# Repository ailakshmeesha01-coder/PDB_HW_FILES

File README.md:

# PDB Hardware Files

KiCad hardware design files for the **NEXUS Power Distribution Board (PDB) V2.0**. The board takes power from a 12S battery (50.4 V max) and distributes it to the humanoid's actuators through 12 XT60 outputs. It precharges the bus, discharges it when powered off, and has a charging input.

**Status:** schematic complete, PCB routed, Gerbers and BOM generated.

## Repository contents

| File / folder | Description |
|---|---|
| `PDB_2.0.kicad_pro` | KiCad project file (open this one) |
| `PDB_2.0.kicad_sch` | Schematic |
| `PDB_2.0.kicad_pcb` | PCB layout (2 layers, 4 oz copper) |
| `PDB_2.0_BOM.xlsx` | Bill of materials |
| `PDB_2.0 Gerber files.zip` | Gerber and drill files for fabrication |
| `NEXUS_PDB_V2_power_simulation.pdf` | Power copper simulation report (current and temperature) |
| `fp-lib-table`, `sym-lib-table` | Project footprint and symbol library tables |
| `Libraries/` | Symbols, footprints and 3D models used by the project |

## Work done

- **Schematic:** full wiring with ERC; precharge, discharge and charging circuits; precharge and charging indicator LEDs added; C21 increased to 1 µF for a reliable power-on reset.
- **PCB layout:** placement, routing and branding; power tracks widened; solid copper pours on the power nets.
- **Main current path:** fixed the via bottleneck between the top-layer MOSFETs and the bottom-layer pours. Added a solid BUS+ pour on F.Cu and more vias on the MOSFET drain and source sides; removed stacked duplicate vias.
- **Connectors:** fixed the XT30 footprint mismatch; added the QS8-S battery connector (J13) and XT90 footprints to `Libraries/`.
- **Assembly:** thermal relief on small SMD GND pads for easier hand soldering; large power pads stay solid.
- **Simulation:** checked the power copper at 100 A continuous and 300 A pulses (see the PDF).
- **Outputs:** Gerbers, 3D models and BOM generated.
- **Project:** files renamed from `PDC_new` to `PDB_2.0`; libraries moved into `Libraries/`.

## Simulation results (summary)

- **100 A continuous** works with a small fan (~1 m/s airflow): peak rise about +36 K. In still air the hottest spots reach about +65 K, which is too hot in a warm enclosure.
- **300 A pulses** of up to ~20 ms are fine (≤ +22 K extra). Avoid 300 A for longer than ~50 ms.
- Hottest areas: MOSFET tabs (U14 most), the J13 battery input, and a narrow BATT+ neck on the bottom layer.

## Open items

- **U4A run latch:** check that it is clocked from `TIMEOUT` with D = `PC_DONE`, so the board can't get stuck in precharge-only mode.
- **Fuses:** F1 and F4 must be rated for **≥ 58 V DC**. Size F1 to the real peak current.
- **Overvoltage:** set the ODrive regen limits and overvoltage trip (or add a brake chopper) to keep BUS+ at or below 50.4 V.
- **Cooling:** plan for airflow across the board if it will run near 100 A continuously.

## Getting started

Requires [KiCad](https://www.kicad.org/download/) **10.0** or newer.

```bash
git clone https://github.com/ailakshmeesha01-coder/PDB_HW_FILES.git
```

Open `PDB_2.0.kicad_pro` in KiCad. Libraries in `Libraries/` load automatically through `${KIPRJMOD}`.

## Contributing

- Save and close KiCad before committing.
- Lock files, backups, local history and `*.kicad_prl` are excluded by `.gitignore`.
- Put new symbols and footprints in `Libraries/`.
- Use clear commit messages, e.g. `sch: fix U4A latch` or `pcb: widen BATT+ neck`.

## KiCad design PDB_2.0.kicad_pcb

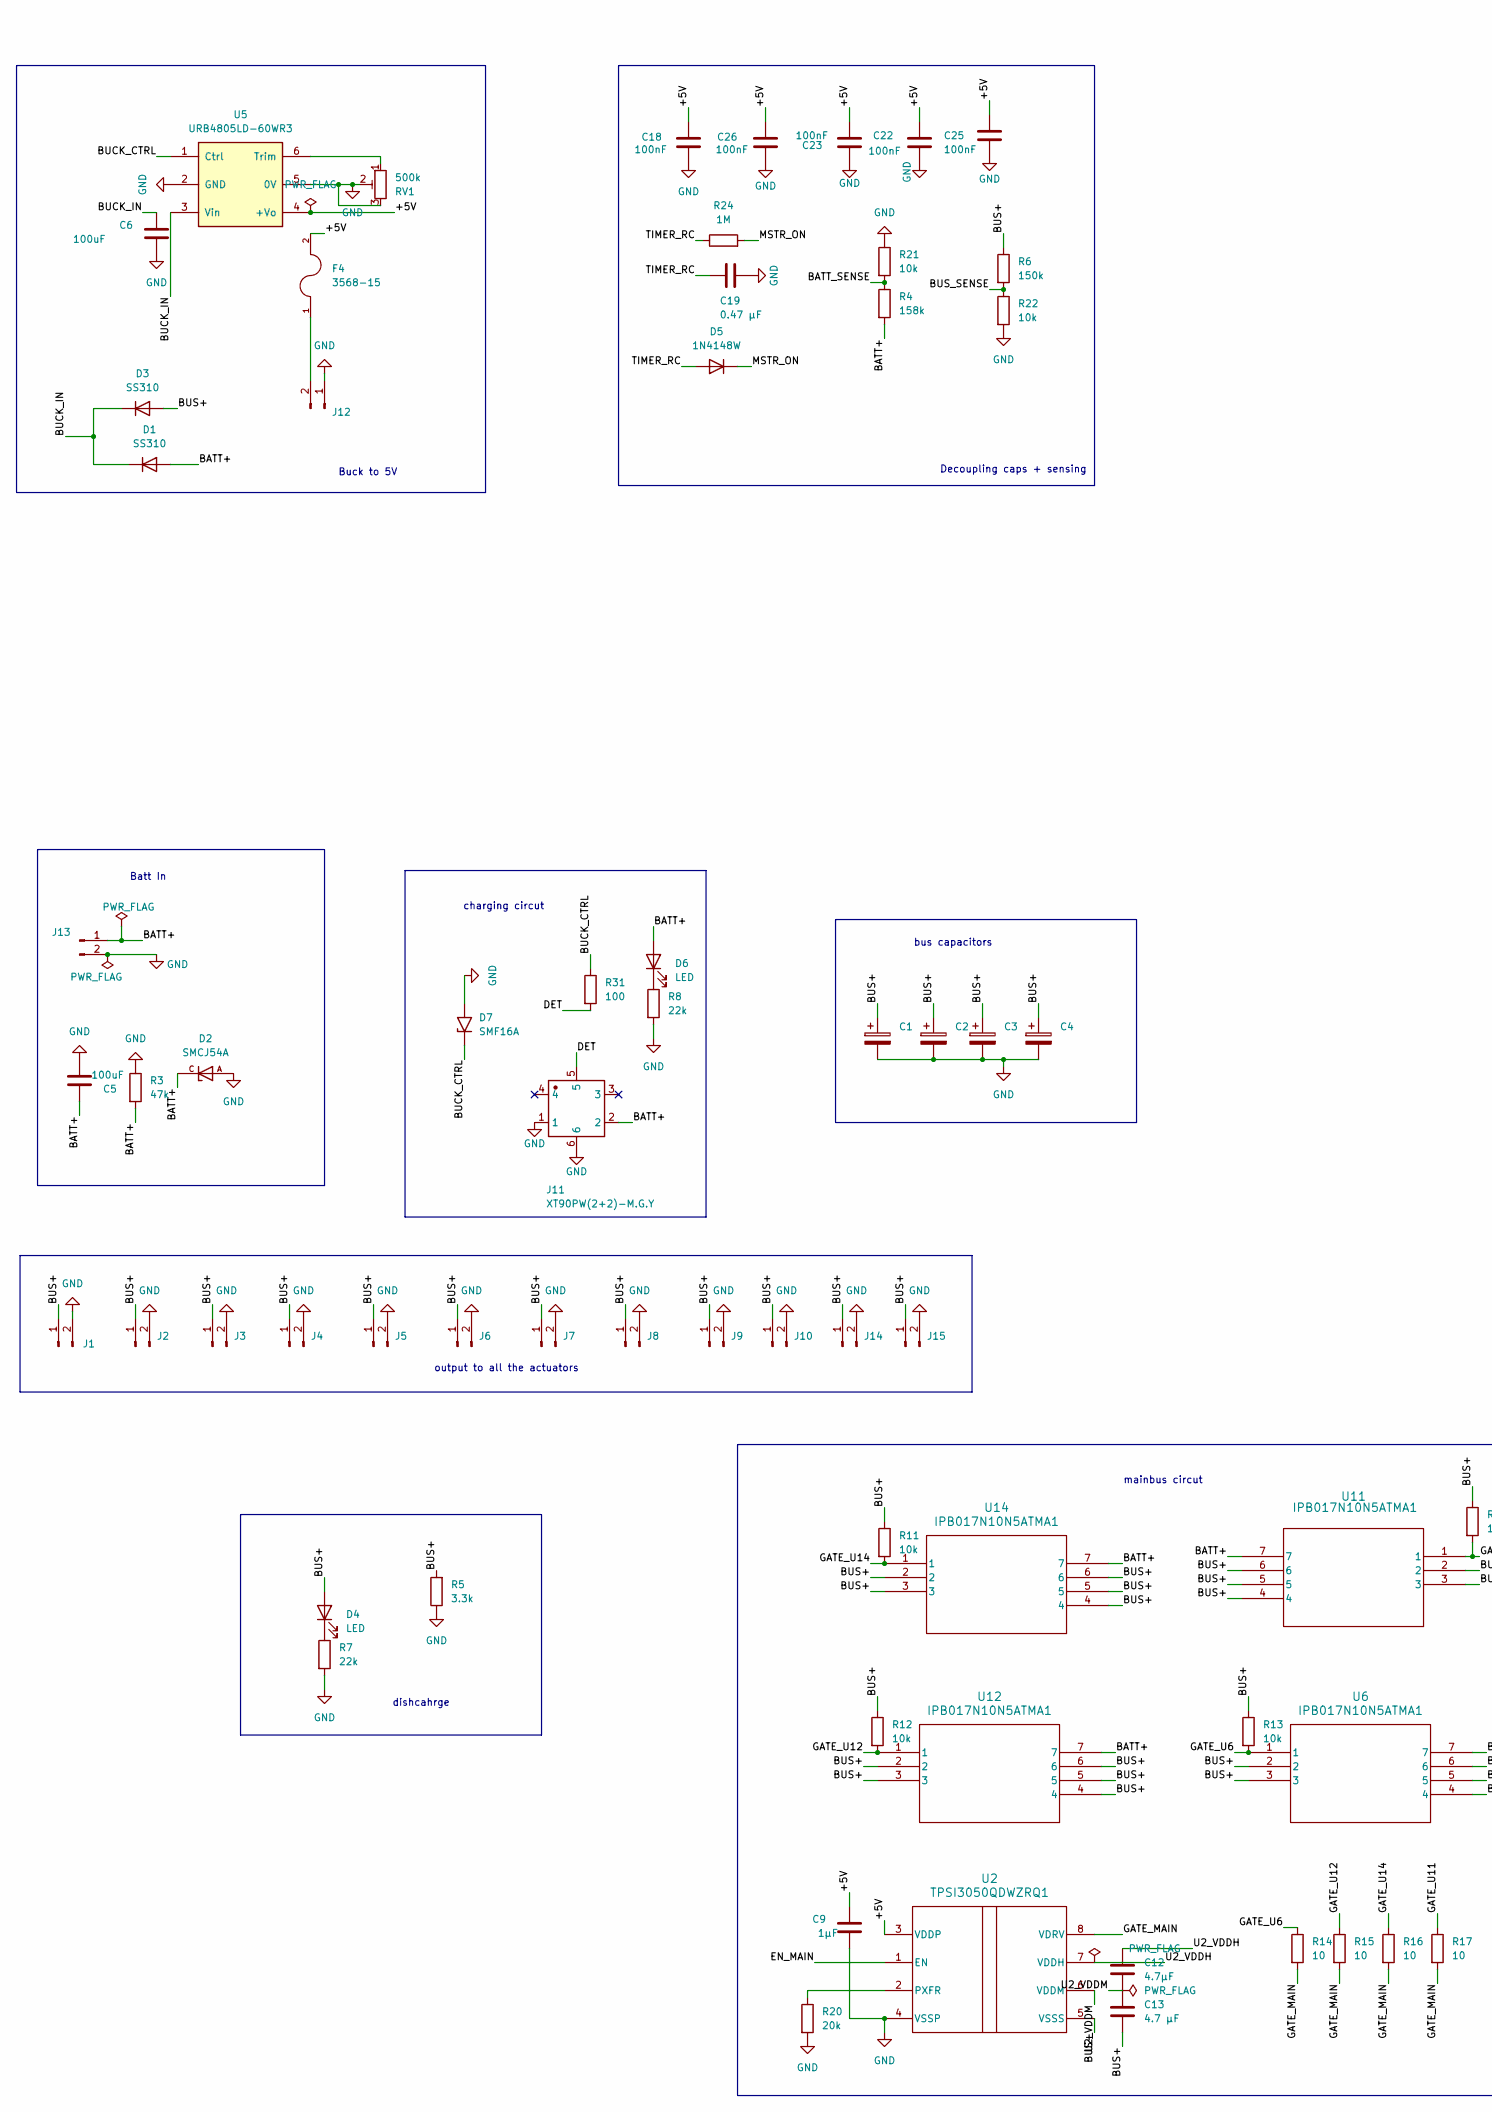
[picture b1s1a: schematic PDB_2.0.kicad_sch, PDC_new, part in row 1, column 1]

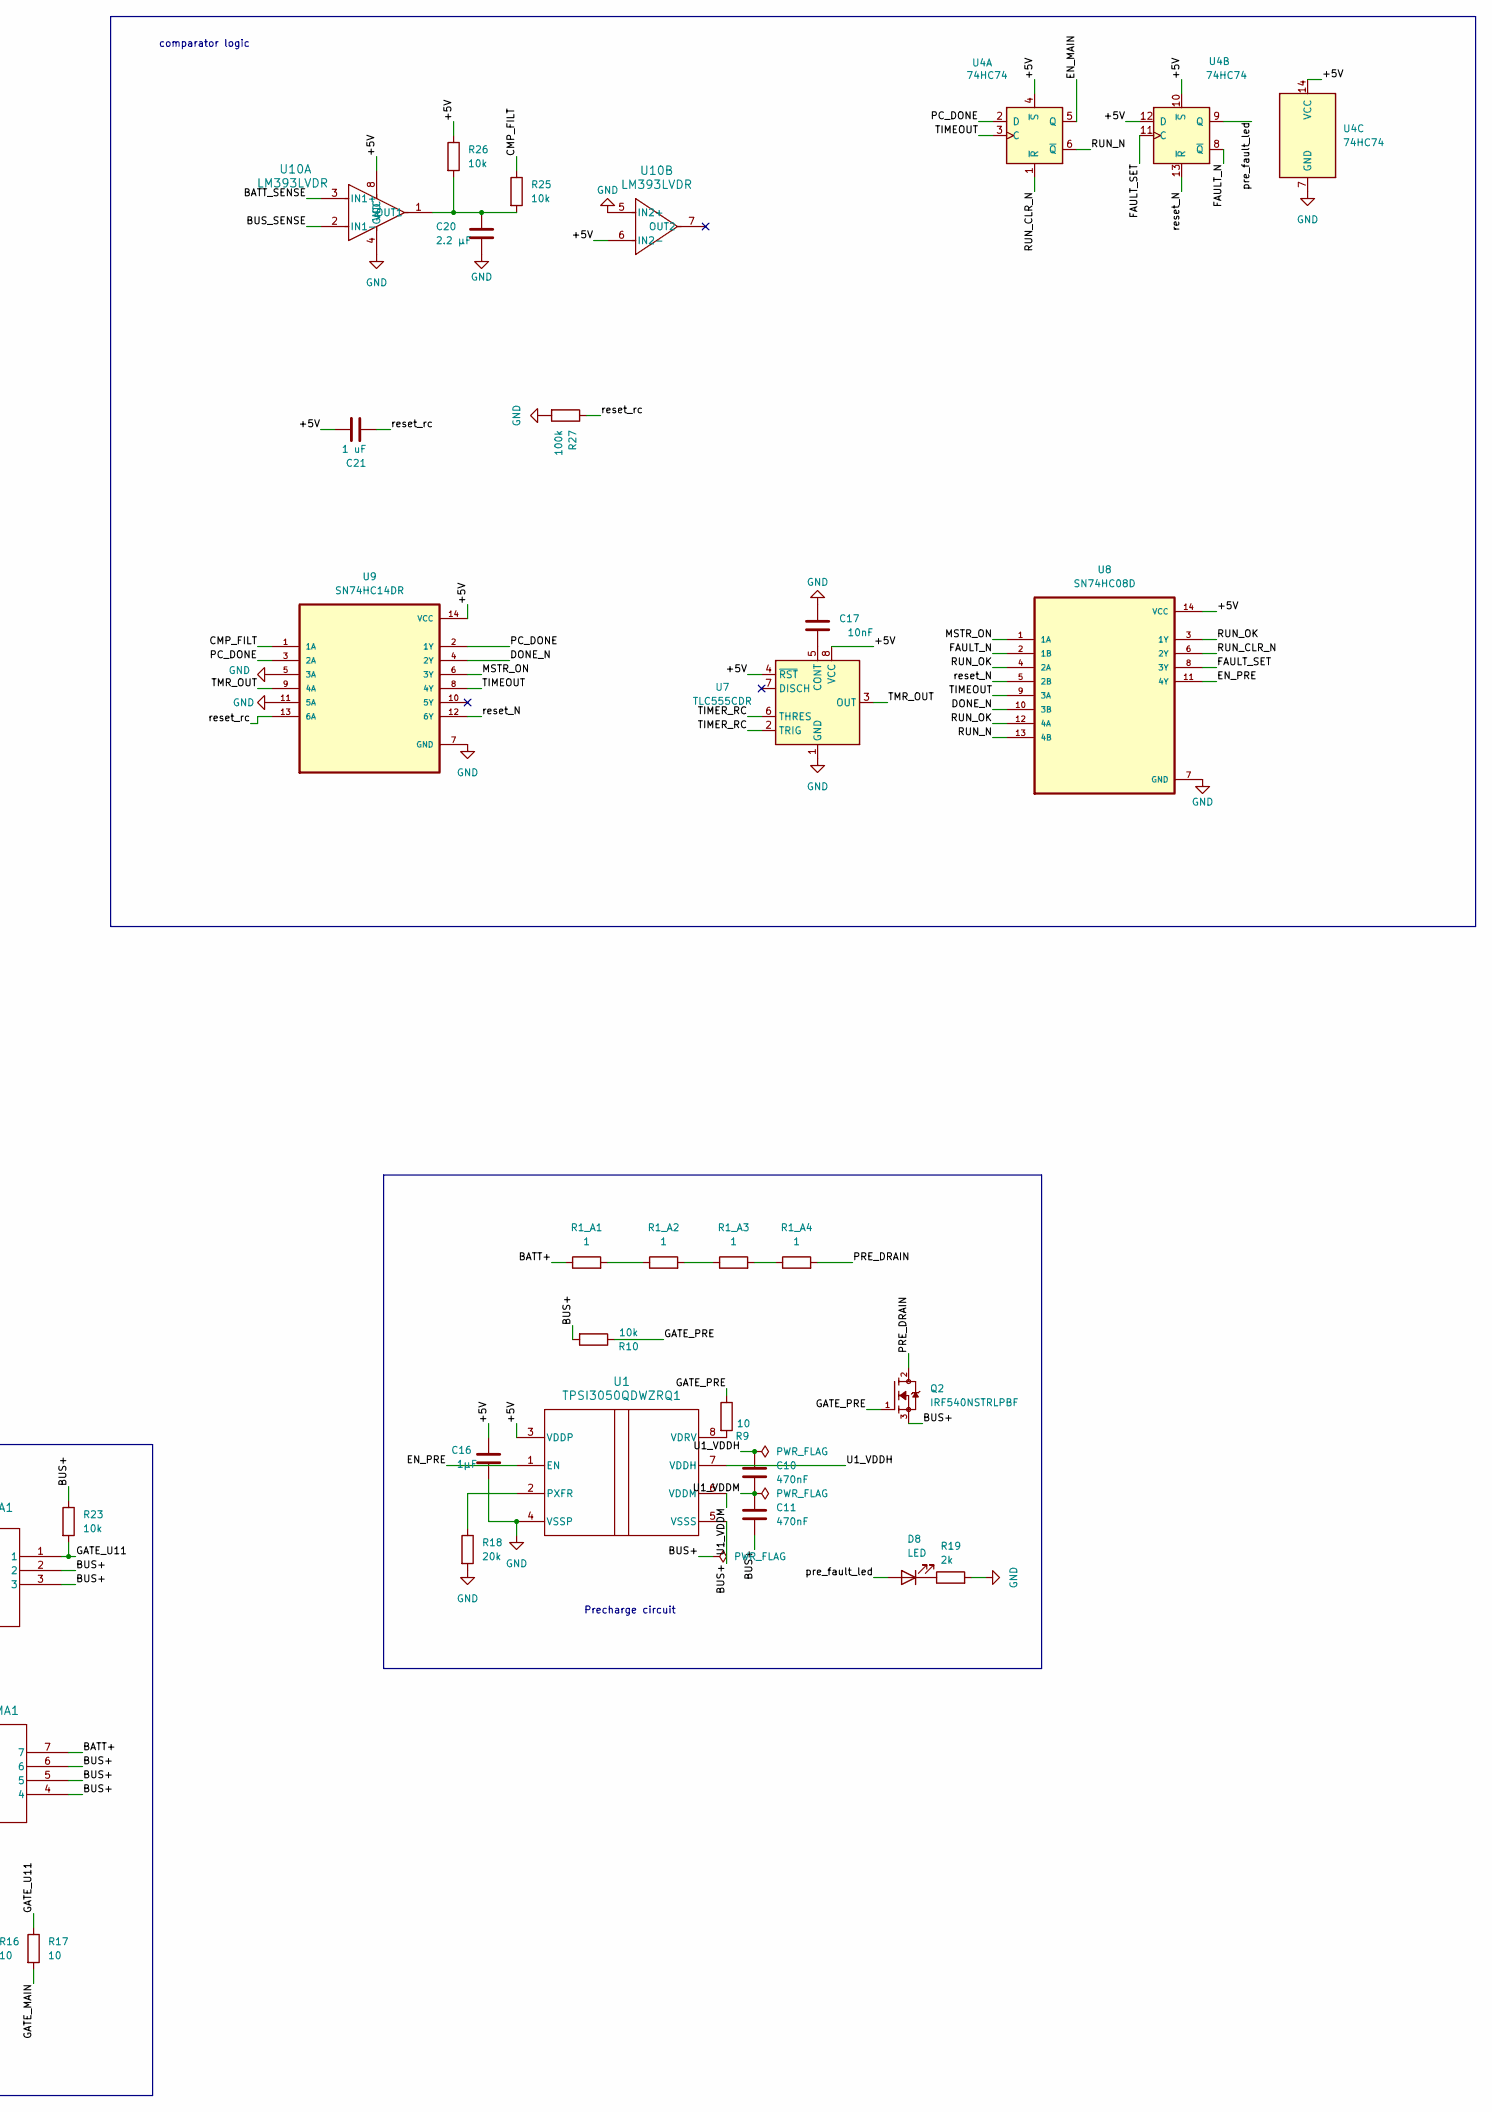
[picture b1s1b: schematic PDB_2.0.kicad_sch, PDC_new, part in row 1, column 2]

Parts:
C1, C2, C3, C4: 1000uF/100V; CP_Radial_D18.0mm_P7.50mm
C5, C6: 100uF; CP_Radial_D10.0mm_P5.00mm
C9, C16: 1µF; C_0805_2012Metric_Pad1.18x1.45mm_HandSolder
C10, C11: 470nF; C_0805_2012Metric_Pad1.18x1.45mm_HandSolder
C12: 4.7µF; C_1206_3216Metric_Pad1.33x1.80mm_HandSolder
C13: 4.7 µF; C_1206_3216Metric_Pad1.33x1.80mm_HandSolder
C17: 10nF; C_0805_2012Metric_Pad1.18x1.45mm_HandSolder
C18, C22, C23, C25, C26: 100nF; C_0805_2012Metric_Pad1.18x1.45mm_HandSolder
C19: 0.47 µF; C_0805_2012Metric_Pad1.18x1.45mm_HandSolder
C20: 2.2 µF; C_0805_2012Metric_Pad1.18x1.45mm_HandSolder
C21: 1 uF; C_0805_2012Metric_Pad1.18x1.45mm_HandSolder
D1, D3: SS310; D_SMA
D2: SMCJ54A; DIOM6859X262N; PARTREV R2102
D4, D6, D8: LED; LED_0805_2012Metric_Pad1.15x1.40mm_HandSolder
D5: 1N4148W; D_SOD-123
D7: SMF16A; D_SOD-123F
F4: 3568-15; Fuseholder_Blade_Mini_Keystone_3568; PARTREV C
J1, J2, J3, J4, J5, J6, J7, J8, J9, J10, J14, J15: Conn_01x02_Pin; AMASS_XT60PW-F_1x02_P7.20mm_Horizontal
J11: XT90PW(2+2)-M.G.Y; CONN-TH_XT90PW2X2-MGY; Manufacturer Part XT90PW(2+2)-M.G.Y
J12: Conn_01x02_Pin; AMASS_XT30PW-F_1x02_P2.50mm_Horizontal
J13: Conn_01x02_Pin; QS8-S-M_Vertical_DirectCup
Q2: IRF540NSTRLPBF; TRANS_IRF540NSTRLPBF; PARTREV 3/18/04
R1_A1, R1_A2, R1_A3, R1_A4: 1; R_Axial_Power_L25.0mm_W9.0mm_P30.48mm
R3: 47k; R_1206_3216Metric_Pad1.30x1.75mm_HandSolder
R4: 158k; R_0805_2012Metric_Pad1.20x1.40mm_HandSolder
R5: 3.3k; R_Axial_Power_L25.0mm_W9.0mm_P30.48mm
R6: 150k; R_0805_2012Metric_Pad1.20x1.40mm_HandSolder
R7, R8: 22k; R_1206_3216Metric_Pad1.30x1.75mm_HandSolder
R9, R14, R15, R16, R17: 10; R_0805_2012Metric_Pad1.20x1.40mm_HandSolder
R10, R11, R12, R13, R21, R22, R23, R25, R26: 10k; R_0805_2012Metric_Pad1.20x1.40mm_HandSolder
R18, R20: 20k; R_0805_2012Metric_Pad1.20x1.40mm_HandSolder
R19: 2k; R_1206_3216Metric_Pad1.30x1.75mm_HandSolder
R24: 1M; R_0805_2012Metric_Pad1.20x1.40mm_HandSolder
R27: 100k; R_0805_2012Metric_Pad1.20x1.40mm_HandSolder
R31: 100; R_0805_2012Metric_Pad1.20x1.40mm_HandSolder
RV1: 500k; Potentiometer_Bourns_3296W_Vertical
U1, U2: TPSI3050QDWZRQ1; DWZ0008A-MFG
U4: 74HC74; SOIC-14_3.9x8.7mm_P1.27mm
U5: URB4805LD-60WR3; URB48_LD-60WR3; MPN URB4805LD-60WR3
U6, U11, U12, U14: IPB017N10N5ATMA1; IPB017N10N5ATMA1_INF
U7: TLC555CDR; SOIC-8_3.9x4.9mm_P1.27mm
U8: SN74HC08D; SOIC127P600X175-14N
U9: SN74HC14DR; SOIC-14_3.9x8.7mm_P1.27mm
U10: LM393LVDR; SOIC-8_3.9x4.9mm_P1.27mm

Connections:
/+5V: C9.1, C16.1, C18.2, C21.2, C22.1, C23.2, C25.2, C26.2, F4.2, R26.1, U1.3 (VDDP), U2.3 (VDDP), U4.4 (~S), U4.10 (~S), U4.12 (D), U4.14 (VCC), U5.4 (+Vo), U7.4 (~RST), U7.8 (VCC), U8.14 (VCC), U9.14 (VCC), U10.6 (IN2-), U10.8 (VCC)
/BATT+: C5.1, D1.2 (A), D2.C, D6.2 (A), J11.2, J13.1, R1_A1.1, R3.2, R4.2, U6.7, U11.7, U12.7, U14.7
/BATT_SENSE: R4.1, R21.2, U10.3 (IN1+)
/BUCK_CTRL: D7.1 (A1), R31.1, U5.1 (Ctrl)
/BUCK_IN: C6.1, D1.1 (K), D3.1 (K), U5.3 (Vin)
/BUS+: C1.1, C2.1, C3.1, C4.1, C11.2, C13.2, D3.2 (A), D4.2 (A), J1.1, J2.1, J3.1, J4.1, J5.1, J6.1, J7.1, J8.1, J9.1, J10.1, J14.1, J15.1, Q2.3, R5.2, R6.1, R10.2, R11.1, R12.1, R13.1, R23.1, U1.5 (VSSS), U2.5 (VSSS), U6.2, U6.3, U6.4, U6.5, U6.6, U11.2, U11.3, U11.4, U11.5, U11.6, U12.2, U12.3, U12.4, U12.5, U12.6, U14.2, U14.3, U14.4, U14.5, U14.6
/BUS_SENSE: R6.2, R22.1, U10.2 (IN1-)
/CMP_FILT: R25.1, U9.1 (1A)
/DET: J11.5, R31.2
/DONE_N: U8.10 (3B), U9.4 (2Y)
/EN_MAIN: U2.1 (EN), U4.5 (Q)
/EN_PRE: U1.1 (EN), U8.11 (4Y)
/FAULT_N: U4.8 (~Q), U8.2 (1B)
/FAULT_SET: U4.11 (C), U8.8 (3Y)
/GATE_MAIN: R14.2, R15.2, R16.2, R17.2, U2.8 (VDRV)
/GATE_PRE: Q2.1, R9.1, R10.1
/GATE_U6: R13.2, R14.1, U6.1
/GATE_U11: R17.1, R23.2, U11.1
/GATE_U12: R12.2, R15.1, U12.1
/GATE_U14: R11.2, R16.1, U14.1
/MSTR_ON: D5.1 (K), R24.2, U8.1 (1A), U9.6 (3Y)
/PC_DONE: U4.2 (D), U9.2 (1Y), U9.3 (2A)
/PRE_DRAIN: Q2.2, R1_A4.2
/RUN_CLR_N: U4.1 (~R), U8.6 (2Y)
/RUN_N: U4.6 (~Q), U8.13 (4B)
/RUN_OK: U8.3 (1Y), U8.4 (2A), U8.12 (4A)
/TIMEOUT: U4.3 (C), U8.9 (3A), U9.8 (4Y)
/TIMER_RC: C19.2, D5.2 (A), R24.1, U7.2 (TRIG), U7.6 (THRES)
/TMR_OUT: U7.3 (OUT), U9.9 (4A)
/U1_VDDH: C10.1, U1.7 (VDDH)
/U1_VDDM: C10.2, C11.1, U1.6 (VDDM)
/U2_VDDH: C12.1, U2.7 (VDDH)
/U2_VDDM: C12.2, C13.1, U2.6 (VDDM)
/pre_fault_led: D8.2 (A), U4.9 (Q)
/reset_N: U4.13 (~R), U8.5 (2B), U9.12 (6Y)
/reset_rc: C21.1, R27.1, U9.13 (6A)
GND: C1.2, C2.2, C3.2, C4.2, C5.2, C6.2, C9.2, C16.2, C17.1, C18.1, C19.1, C20.1, C22.2, C23.1, C25.1, C26.1, D2.A, D7.2 (A2), J1.2, J2.2, J3.2, J4.2, J5.2, J6.2, J7.2, J8.2, J9.2, J10.2, J11.1, J11.6, J12.1, J13.2, J14.2, J15.2, R3.1, R5.1, R7.2, R8.2, R18.2, R19.2, R20.2, R21.1, R22.2, R27.2, RV1.2, RV1.3, U1.4 (VSSP), U2.4 (VSSP), U4.7 (GND), U5.2 (GND), U5.5 (0V), U7.1 (GND), U8.7 (GND), U9.5 (3A), U9.7 (GND), U9.11 (5A), U10.4 (GND), U10.5 (IN2+)
unnamed: D4.1 (K), R7.1
unnamed: D6.1 (K), R8.1
unnamed: D8.1 (K), R19.1
unnamed: F4.1, J12.2
unnamed: R1_A1.2, R1_A2.1
unnamed: R1_A2.2, R1_A3.1
unnamed: R1_A3.2, R1_A4.1
unnamed: R18.1, U1.2 (PXFR)
unnamed: R9.2, U1.8 (VDRV)
unnamed: R20.1, U2.2 (PXFR)
unnamed: RV1.1, U5.6 (Trim)
unnamed: C17.2, U7.5 (CONT)
unnamed: C20.2, R25.2, R26.2, U10.1 (OUT1)

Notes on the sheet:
charging circut
Precharge circuit
Batt In
mainbus circut
bus capacitors
Decoupling caps + sensing
Buck to 5V
dishcahrge
output to all the actuators
comparator logic

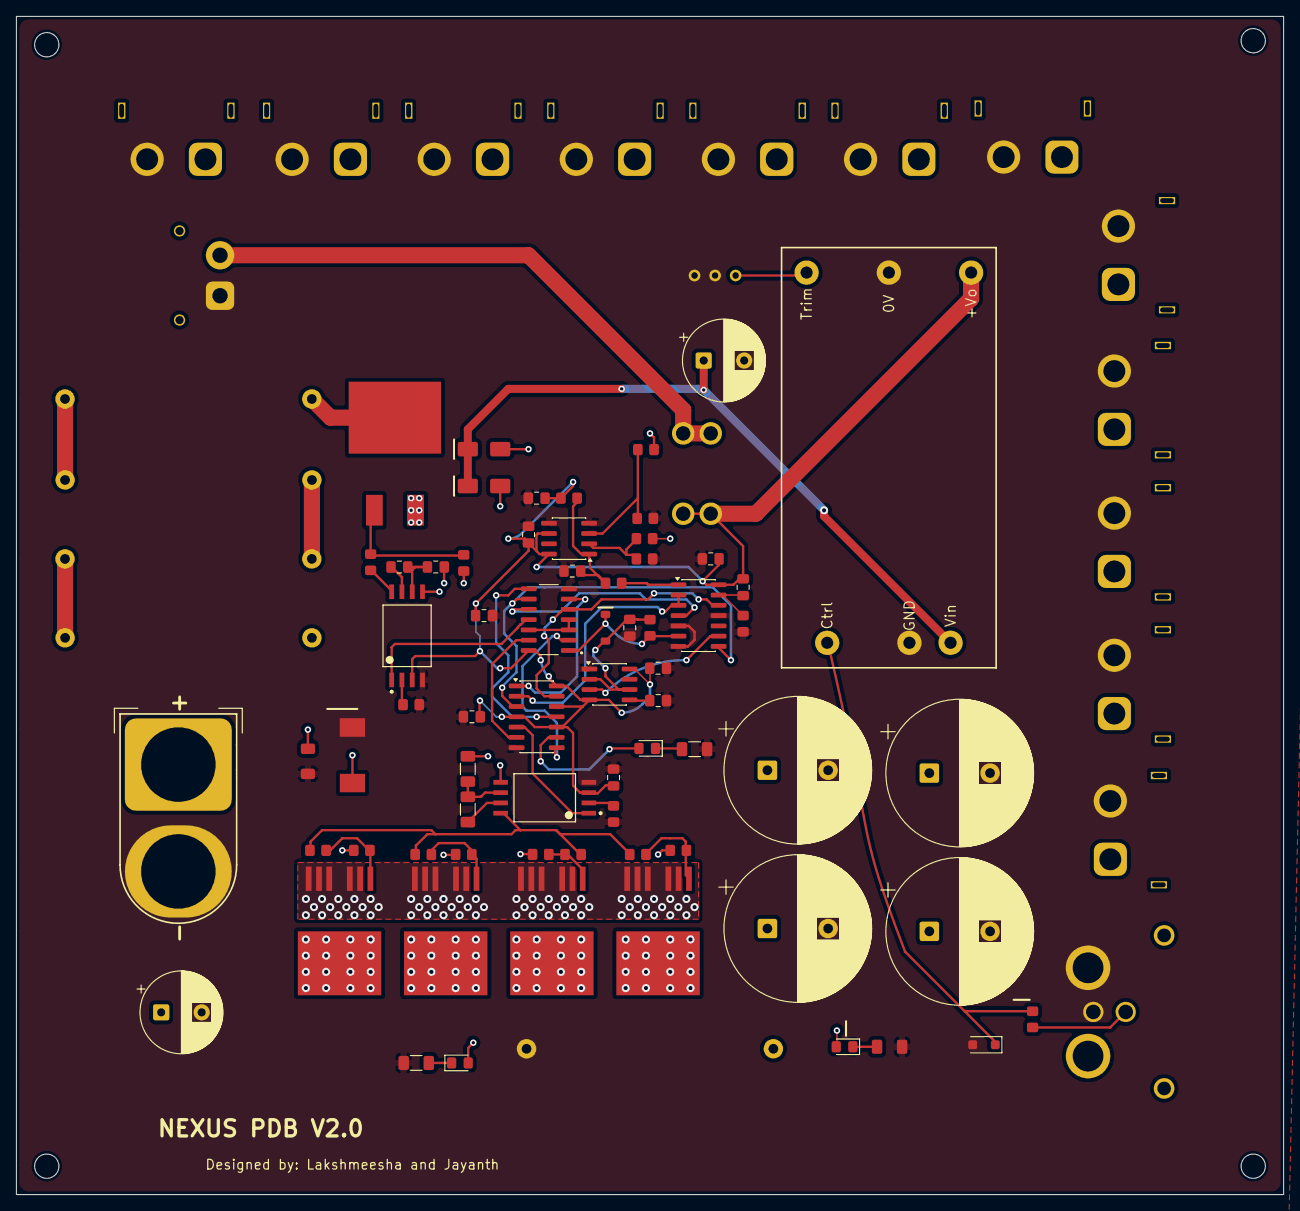
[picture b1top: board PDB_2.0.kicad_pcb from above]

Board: 2 copper layers, 156.5 x 145.5 mm, 89 parts (0 on the bottom side), 50 nets.

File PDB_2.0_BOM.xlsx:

# | Reference | Qty | Value | Footprint | Supplier / Part No. | Link | Notes
1 | C1, C2, C3, C4 | 4 | 1000uF/100V | Capacitor_THT:CP_Radial_D18.0mm_P7.50mm |  | https://www.digikey.in/en/products/detail/nichicon/UVR2A102M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
2 | C5,C6 | 2 | 100uF | Capacitor_THT:CP_Radial_D10.0mm_P5.00mm |  | https://www.digikey.in/en/products/result?keywords=EEU-FC2A101L
3 | C9 | 1 | 1µF | Capacitor_SMD:C_0805_2012Metric_Pad1.18x1.45mm_HandSolder |  | https://robu.in/product/grm21br71h105ka12l-murata-electronic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
4 | C10, C11 | 2 | 470nF | Capacitor_SMD:C_0805_2012Metric_Pad1.18x1.45mm_HandSolder |  | https://robu.in/product/gcm21br71h474ka55l-murata-electronic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
5 | C12 | 1 | 4.7µF | Capacitor_SMD:C_1206_3216Metric_Pad1.33x1.80mm_HandSolder |  | https://robu.in/product/grm31cr71h475ka12l-murata-smd-multil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
6 | C13 | 1 | 4.7 µF | Capacitor_SMD:C_1206_3216Metric_Pad1.33x1.80mm_HandSolder |  | https://robu.in/product/grm31cr71h475ka12l-murata-smd-multil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
7 | C16,C21 | 2 | 1µF | Capacitor_SMD:C_0805_2012Metric_Pad1.18x1.45mm_HandSolder |  | https://robu.in/product/08051c105k4t2a-kyocera-avx-cap-smd-m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
8 | C17 | 1 | 10nF | Capacitor_SMD:C_0805_2012Metric_Pad1.18x1.45mm_HandSolder |  | https://robu.in/product/gcj21br72e103kxj3l-murata-electronic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
9 | C18, C22, C23, C25, C26 | 5 | 100nF | Capacitor_SMD:C_0805_2012Metric_Pad1.18x1.45mm_HandSolder |  | https://robu.in/product/cc0805krx7r9bb104-yageo-smd-multilay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
10 | C19 | 1 | 0.47 µF | Capacitor_SMD:C_0805_2012Metric_Pad1.18x1.45mm_HandSolder |  | https://robu.in/product/gcm21br71h474ka55l-murata-electronic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
11 | C20 | 1 | 2.2 µF | Capacitor_SMD:C_0805_2012Metric_Pad1.18x1.45mm_HandSolder |  | https://robu.in/product/cl21b225kbynnwe-samsang-50v-2-2uf-x7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
12 | D1, D3 | 2 | SS310 | Diode_SMD:D_SMA |  | https://www.digikey.in/en/products/detail/taiwan-semiconduct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
13 | D2 | 1 | SMCJ54A | SMCJ54A:DIOM6859X262N |  | https://www.digikey.in/en/products/detail/littelfuse-inc/SMC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
14 | D4 | 1 | LED | LED_SMD:LED_0805_2012Metric_Pad1.15x1.40mm_HandSolder |  | https://robu.in/product/17-215uyc-s530-a3-tr8-everlight-yell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 | yellow
15 | D5 | 1 | 1N4148W | Diode_SMD:D_SOD-123 |  | https://robu.in/product/1n4148w-7-f-diodes-incorporated-100v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
16 | D6 | 1 | LED | LED_SMD:LED_0805_2012Metric_Pad1.15x1.40mm_HandSolder |  | https://robu.in/product/17-21-t1d-cp2r1ty-3t-everlight-white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 | white
17 | D7 | 1 | SMF16A | D_SOD-123F |  | https://robu.in/product/smf16a-littelfuse-smf16a-tvs-diode-s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
18 | D8 | 1 | LED | LED_SMD:LED_0805_2012Metric_Pad1.15x1.40mm_HandSolder |  | https://robu.in/product/17-215-r6c-aq1r2b-3t-everlight-red-6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 | red
19 | F4 | 1 | 3568-15 | Fuse:Fuseholder_Blade_Mini_Keystone_3568 |  | https://www.digikey.in/en/products/detail/keystone-electroni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
20 | J1, J2, J3, J4, J5, J6, J7, J8, J9, J10, J14, J15 | 12 | Conn_01x02_Pin | Connector_AMASS:AMASS_XT60PW-F_1x02_P7.20mm_Horizontal |  | https://robu.in/product/amass-xt60pw30-female-connector-xt60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
21 | J11 | 1 | XT90PW(2+2)-M.G.Y | XT90PW(2+2)-M.G.Y:CONN-TH_XT90PW2X2-MGY |  | https://robu.in/product/amass-xt90pw22-male-connector-xt9022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
22 | J12 | 1 | Conn_01x02_Pin | Connector_AMASS:AMASS_XT30PW-F_1x02_P2.50mm_Horizontal |  | https://robu.in/product/amass-xt30pw30-female-connector-xt30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
23 | J13 | 1 | Conn_01x02_Pin | QS8_S_Connectors:QS8-S-M_Vertical_DirectCup |  | https://robu.in/product/qs8-anti-spark-180a-high-current-gol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
24 | Q2 | 1 | IRF540NSTRLPBF | IRF540NSTRLPBF:TRANS_IRF540NSTRLPBF |  | https://www.digikey.in/en/products/detail/infineon-technolog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
25 | R1A1,R1A2,R1A3,R1A4 | 4 | 1 OR 0.5 | Resistor_THT:R_Axial_Power_L25.0mm_W9.0mm_P30.48mm |  | https://robu.in/product/0-5-ohm-5-watt-wire-wound-resistor-p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
26 | R3 | 1 | 47k | Resistor_SMD:R_1206_3216Metric_Pad1.30x1.75mm_HandSolder |  | https://robu.in/product/rc1206fr-0747kl-yageo-smd-chip-resis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
27 | R4 | 1 | 158k | Resistor_SMD:R_0805_2012Metric_Pad1.20x1.40mm_HandSolder |  | https://robu.in/product/rc0805fr-07158kl-yageo-smd-chip-resi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
28 | R5 | 1 | 3.3k | Resistor_THT:R_Axial_Power_L25.0mm_W9.0mm_P30.48mm |  | https://www.mouser.in/en/ProductDetail/Bourns/WS5M3301J?qs=R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
29 | R6 | 1 | 150k | Resistor_SMD:R_0805_2012Metric_Pad1.20x1.40mm_HandSolder |  | https://robu.in/product/rc0805fr-07150kl-yageo-res-thick-fil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
30 | R7,R8 | 2 | 22k | Resistor_SMD:R_1206_3216Metric_Pad1.30x1.75mm_HandSolder |  | https://robu.in/product/rc1206jr-0722kl-yageo-smd-chip-resis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
31 | R9, R14, R15, R16, R17 | 5 | 10 | Resistor_SMD:R_0805_2012Metric_Pad1.20x1.40mm_HandSolder |  | https://robu.in/product/rt0805drd0710rl-yageo-smd-chip-resis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
32 | R10, R11, R12, R13, R21, R22, R23, R25, R26 | 9 | 10k | Resistor_SMD:R_0805_2012Metric_Pad1.20x1.40mm_HandSolder |  | https://robu.in/product/ac0805fr-0710kl-yageo-res-thick-film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
33 | R19 | 1 | 2k | Resistor_SMD:R_1206_3216Metric_Pad1.30x1.75mm_HandSolder |  | https://robu.in/product/2-2k-ohm-1-4w-1206-surface-mount-chi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
34 | R18, R20 | 2 | 20k | Resistor_SMD:R_0805_2012Metric_Pad1.20x1.40mm_HandSolder |  | https://robu.in/product/rc0805fr-0720kl-yageo-res-thick-film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
35 | R24 | 1 | 1M | Resistor_SMD:R_0805_2012Metric_Pad1.20x1.40mm_HandSolder |  | https://robu.in/product/rc0805fr-071ml-yageo-res-thick-film-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
36 | R27 | 1 | 100k | Resistor_SMD:R_0805_2012Metric_Pad1.20x1.40mm_HandSolder |  | https://robu.in/product/rc0805dr-07100kl-yageo-125mw-thick-f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
37 | R31 | 1 | 100 | Resistor_SMD:R_0805_2012Metric_Pad1.20x1.40mm_HandSolder |  | https://robu.in/product/rc0805fr-7w100rl-yageo-smd-chip-resi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
38 | RV1 | 1 | 500k | Potentiometer_THT:Potentiometer_Bourns_3296W_Vertical |  | https://robu.in/product/trimpot-multi-turn-cermet-top-adjust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
39 | U1, U2 | 2 | TPSI3050QDWZRQ1 | ul_TPSI3050QDWZRQ1:DWZ0008A-MFG |  | https://www.digikey.in/en/products/detail/texas-instruments/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
40 | U4 | 1 | 74HC74 | Package_SO:SOIC-14_3.9x8.7mm_P1.27mm |  | https://www.digikey.in/en/products/result?keywords=SN74HC74DR
41 | U5 | 1 | URB4805LD-60WR3 | URB4805LD-60WR3:URB48_LD-60WR3 |  | https://www.digikey.in/en/products/detail/mornsun-america-ll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
42 | U6, U11, U12, U14 | 4 | IPB017N10N5ATMA1 | ul_IPB017N10N5ATMA1:IPB017N10N5ATMA1_INF |  | https://www.digikey.in/en/products/result?keywords=IPB017N10N5ATMA1
43 | U7 | 1 | TLC555CDR | Package_SO:SOIC-8_3.9x4.9mm_P1.27mm |  | https://www.digikey.in/en/products/result?keywords=TLC555CDR
44 | U8 | 1 | SN74HC08D | SN74HC08D:SOIC127P600X175-14N |  | https://robu.in/product/sn74hc08dr-texas-instruments-logic-i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
45 | U9 | 1 | SN74HC14DR | Package_SO:SOIC-14_3.9x8.7mm_P1.27mm |  | https://www.digikey.in/en/products/detail/texas-instruments/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
46 | U10 | 1 | LM393LVDR | Package_SO:SOIC-8_3.9x4.9mm_P1.27mm |  | https://www.digikey.in/en/products/detail/texas-instruments/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
 | Total components | 89
